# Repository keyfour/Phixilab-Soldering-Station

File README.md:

# Phixilab-Soldering-Station

Hardware desing for soldering station

* [Documentation](doc/README.md)

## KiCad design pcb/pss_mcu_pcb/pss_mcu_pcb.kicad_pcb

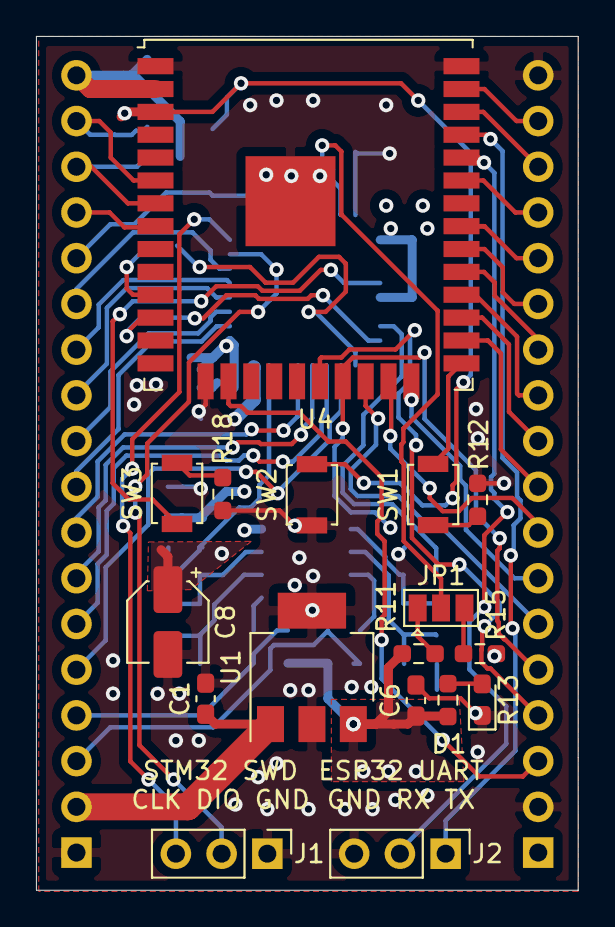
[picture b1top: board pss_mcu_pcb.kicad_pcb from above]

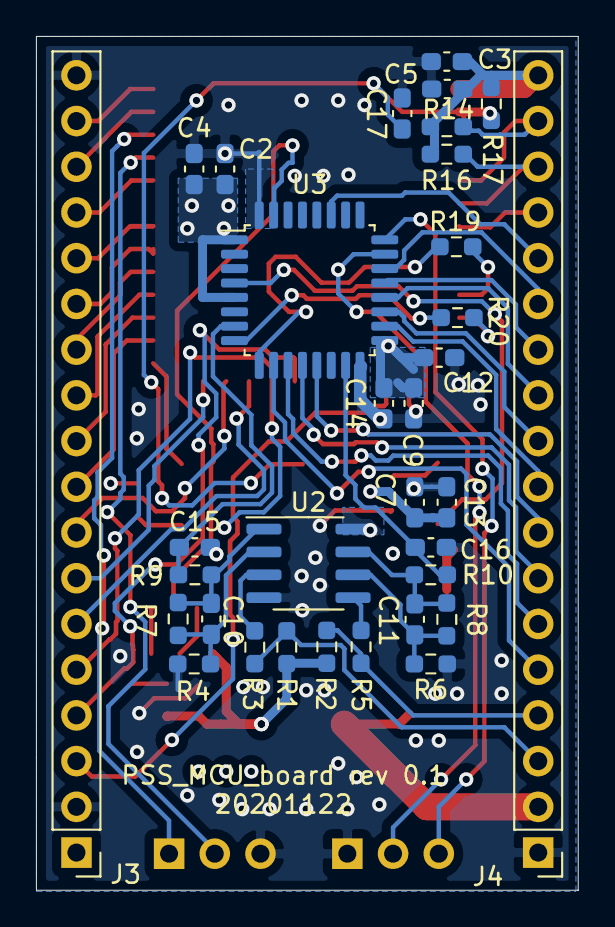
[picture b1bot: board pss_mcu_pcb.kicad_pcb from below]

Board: 4 copper layers, 30.1 x 47.4 mm, 50 parts (33 on the bottom side), 58 nets.

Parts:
C1: 0.47u; C_0603_1608Metric_Pad1.08x0.95mm_HandSolder
C2, C10, C11, C15, C16: 10n; C_0603_1608Metric_Pad1.08x0.95mm_HandSolder
C3, C17: 10u; C_0603_1608Metric_Pad1.08x0.95mm_HandSolder
C4: 1u; C_0603_1608Metric_Pad1.08x0.95mm_HandSolder
C5: 0.1u; C_0603_1608Metric_Pad1.08x0.95mm_HandSolder
C6: 33u; C_0603_1608Metric_Pad1.08x0.95mm_HandSolder
C7, C13: 0.15u; C_0603_1608Metric_Pad1.08x0.95mm_HandSolder
C8: 10u 16V; CP_Elec_4x5.3
C9, C12: 100n; C_0603_1608Metric_Pad1.08x0.95mm_HandSolder
C14: 4.7u; C_0603_1608Metric_Pad1.08x0.95mm_HandSolder
D1: LED; LED_0603_1608Metric_Pad1.05x0.95mm_HandSolder
J1: STM32_Prog; PinHeader_1x03_P2.54mm_Vertical
J2: UART_Prog; PinHeader_1x03_P2.54mm_Vertical
J3, J4: Conn_01x18; PinHeader_1x18_P2.54mm_Vertical
JP1: Jumper_NC_Dual; SolderJumper-3_P1.3mm_Open_Pad1.0x1.5mm
R1, R2, R7, R8: 100k; R_0603_1608Metric_Pad0.98x0.95mm_HandSolder
R3, R4, R5, R6, R9, R10, R11, R12, R15, R18: 1k; R_0603_1608Metric_Pad0.98x0.95mm_HandSolder
R13: 100; R_0603_1608Metric_Pad0.98x0.95mm_HandSolder
R14, R16: 10k; R_0603_1608Metric_Pad0.98x0.95mm_HandSolder
R17: 51k; R_0603_1608Metric_Pad0.98x0.95mm_HandSolder
R19, R20: 10; R_0603_1608Metric_Pad0.98x0.95mm_HandSolder
SW1: Boot; SW_SPST_B3U-1000P
SW2: EN; SW_SPST_B3U-1000P
SW3: SW_Push; SW_SPST_B3U-1000P
U1: LM3940IMP-3.3_NOPB; SOT-223
U2: LM358; SOIC-8_3.9x4.9mm_P1.27mm
U3: STM32F030K6Tx; LQFP-32_7x7mm_P0.8mm
U4: ESP32-WROOM-32U

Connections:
+3V3: C2.1, C3.1, C4.1, C5.1, C6.1, C7.1, C8.1, C9.1, C12.1, C13.1, C14.1, J3.1, J4.18, R1.1, R2.1, R11.2, R13.2, R14.1, R16.1, R17.1, U1.3, U2.8, U3.1, U3.5, U3.17, U4.2
+5V: C1.1, J4.2, U1.1
Boot: SW1.2, U4.25
DISP_CS: J3.17, U4.37
DISP_DC_RS: J3.15, U4.33
DISP_RST: J3.16, U4.36
DISP_SCK: J3.13, U4.30
DISP_SDI: J3.14, U4.31
DISP_SDO: J3.12, U4.29
DISP_T_CLK: J3.11, U4.28
DISP_T_CS: J3.10, U4.27
DISP_T_DIN: J3.9, U4.26
DISP_T_DO: J3.8, U4.23
DISP_T_IRQ: J3.7, U4.24
EN: C17.1, R17.2, SW2.2, U4.3
ESP32_UART_RX: R20.1, U4.12
ESP32_UART_TX: R19.1, U4.11
Fan_PWM: J4.12, U3.21
GND: C1.2, C2.2, C3.2, C4.2, C5.2, C6.2, C7.2, C8.2, C9.2, C12.2, C13.2, C14.2, C15.2, C16.2, C17.2, D1.1, J1.1, J2.3, J3.2, J3.18, J4.1, R4.1, R6.1, R12.2, R15.1, R18.1, SW2.1, U1.2, U1.4, U2.4, U3.16, U3.32, U4.1, U4.15, U4.38, U4.39
Heater_PWM: J4.7, U3.12
HotA_Enc_A: J4.8, U3.13
HotA_Enc_B: J4.14, U3.27
HotA_Switch: J4.11, U3.20
Hot_Air_Reed: J4.13, U3.22
Hot_Air_Themp_ADC: C16.1, R10.1, U3.15
Hot_Air_Therm_Pos: J4.4, R2.2, R5.2
Iron_Themp_ADC: C15.1, R9.1, U3.7
Iron_Therm_Pos: J4.3, R1.2, R3.2
Main_Enc_A: J4.17, R14.2, U4.6
Main_Enc_B: J4.16, R16.2, U4.7
Main_Switch: J4.15, U4.8
unnamed: C10.1, R4.2, R7.2, U2.2
unnamed: C10.2, R7.1, R9.2, U2.1
unnamed: C11.1, R6.2, R8.2, U2.6
unnamed: C11.2, R8.1, R10.2, U2.7
unnamed: D1.2, R13.1
unnamed: JP1.1, R11.1
unnamed: JP1.3, R15.2
unnamed: R3.1, U2.3
unnamed: R5.1, U2.5
unnamed: R12.1, SW1.1
unnamed: R18.2, SW3.2
RXD: J2.2, U4.34
SD_CS: J3.3, U4.16
SD_SCK: J3.4, U4.20
SD_SDI: J3.5, U4.21
SD_SDO: J3.6, U4.22
STM_BOOT: JP1.2, U3.31
STM_RST: SW3.1, U3.4
STM_SWCLK: J1.3, U3.24
STM_SWDIO: J1.2, U3.23
STM_UART_RX: R19.2, U3.9
STM_UART_TX: R20.2, U3.8
Sold_Enc_A: J4.10, U3.19
Sold_Enc_B: J4.9, U3.18
Sold_PWM: J4.5, U3.10
Sold_Switch: J4.6, U3.11
TXD: J2.1, U4.35

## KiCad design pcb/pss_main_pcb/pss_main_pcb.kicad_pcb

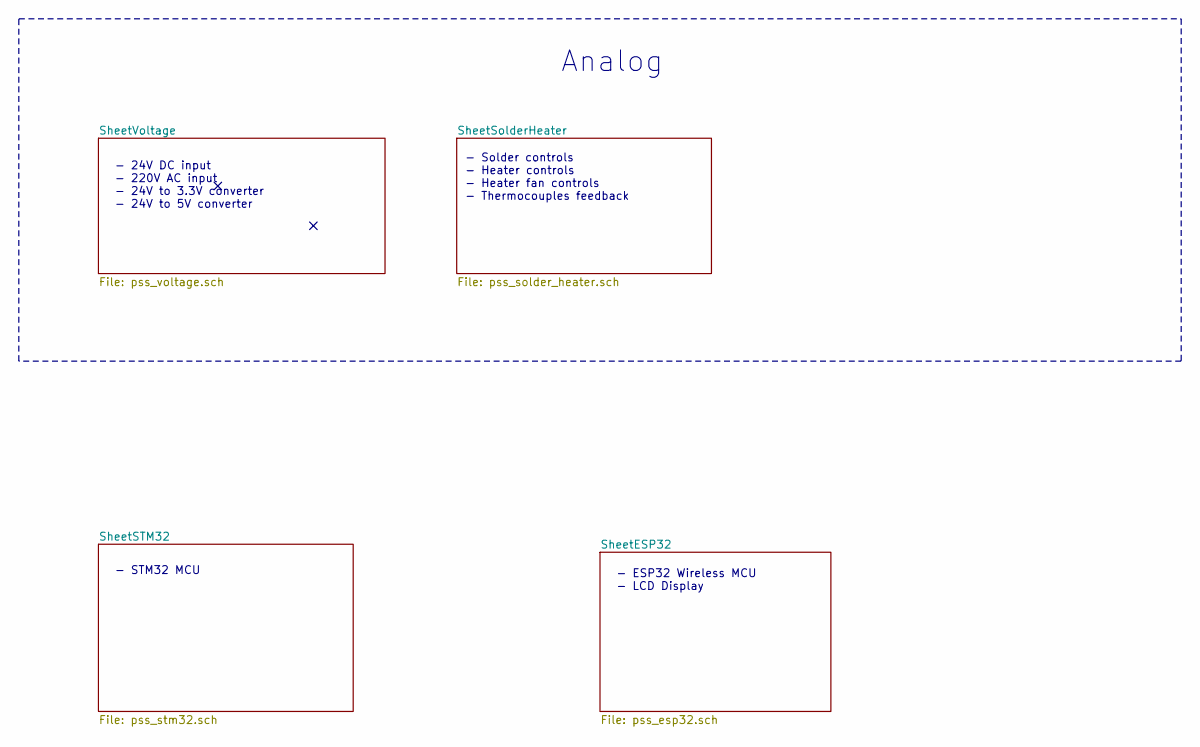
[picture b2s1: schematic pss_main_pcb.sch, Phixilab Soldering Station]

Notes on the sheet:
- 24V DC input - 220V AC input - 24V to 3.3V converter - 24V to 5V converter
- Solder controls - Heater controls - Heater fan controls - Thermocouples feedback
Analog
- STM32 MCU
- ESP32 Wireless MCU - LCD Display

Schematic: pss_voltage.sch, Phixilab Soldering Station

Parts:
C1: 470u 35V; CP_Elec_10x10.5
C2: 270u 10V; CP_Elec_8x10.5
C3: 330u 10V; CP_Elec_8x10.5
D1, D2: SS34; D_SMA_Handsoldering
J1: 24V DC Input; AMASS_XT30U-F_1x02_P5.0mm_Vertical
J2: 220V AC Input; SolderWire-2.5sqmm_1x03_P7.2mm_D2.4mm_OD3.6mm
L1: 68u; L_Taiyo-Yuden_NR-30xx_HandSoldering
L2: 47u; L_Taiyo-Yuden_NR-30xx_HandSoldering
R1: 1k; R_1206_3216Metric_Pad1.42x1.75mm_HandSolder
U1: LM2596S-5; TO-263-5_TabPin3
U2: LM2596S-3.3; TO-263-5_TabPin3

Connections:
220V_Heater2: J2.2; also elsewhere on the board
220_AC1: J2.3; also elsewhere on the board
+3V3: U2.3; also elsewhere on the board
BOOST: U1.6; also elsewhere on the board
FB: U1.12; also elsewhere on the board
GNDPWR: J2.1; also elsewhere on the board
SHDN: D1.3, R1.2, U1.15; also elsewhere on the board

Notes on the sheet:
Voltage Inputs
5V Regulator Output
3.3V Regulator Output

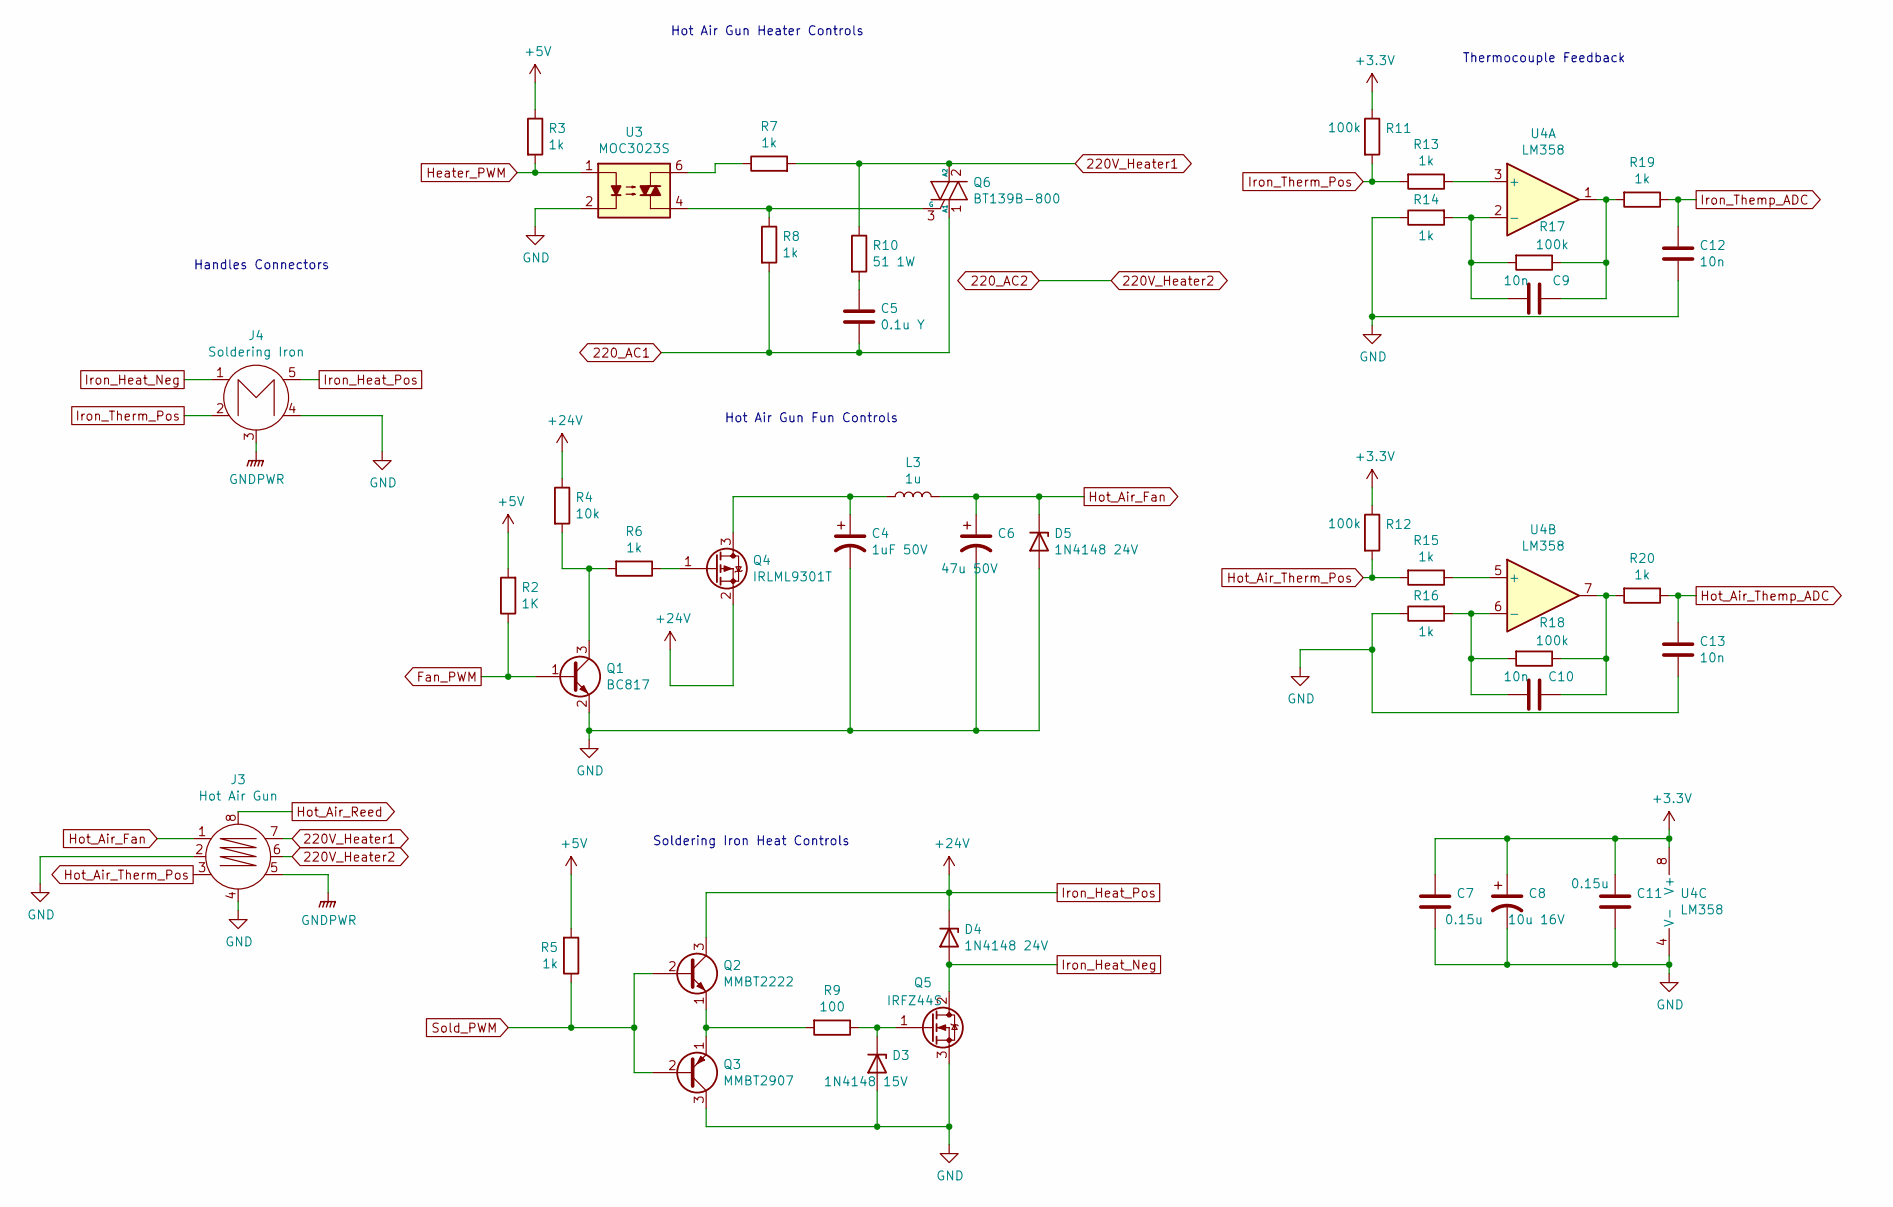
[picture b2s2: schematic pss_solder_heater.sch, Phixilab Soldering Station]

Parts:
C4: 1uF 50V; CP_Elec_4x5.4
C5: 0.1u Y; C_Rect_L10.0mm_W2.5mm_P7.50mm_MKS4
C6: 47u 50V; CP_Elec_8x10.5
C7, C11: 0.15u; C_1206_3216Metric_Pad1.42x1.75mm_HandSolder
C8: 10u 16V; CP_Elec_4x5.4
C9, C10, C12, C13: 10n; C_1206_3216Metric_Pad1.42x1.75mm_HandSolder
D3: 1N4148 15V; D_1206_3216Metric_Pad1.42x1.75mm_HandSolder
D4, D5: 1N4148 24V; D_1206_3216Metric_Pad1.42x1.75mm_HandSolder
J3: Hot Air Gun; GX16-8
J4: Soldering Iron; GX16-5
L3: 1u; L_Taiyo-Yuden_NR-30xx_HandSoldering
Q1: BC817; SOT-23_Handsoldering
Q2: MMBT2222; SOT-23_Handsoldering
Q3: MMBT2907; SOT-23_Handsoldering
Q4: IRLML9301T; SOT-23_Handsoldering
Q5: IRFZ44S; TO-263-2
Q6: BT139B-800; D2PAK-3
R2: 1K; R_1206_3216Metric_Pad1.42x1.75mm_HandSolder
R3, R5, R6, R7, R8, R13, R14, R15, R16, R19, R20: 1k; R_1206_3216Metric_Pad1.42x1.75mm_HandSolder
R4: 10k; R_1206_3216Metric_Pad1.42x1.75mm_HandSolder
R9: 100; R_1206_3216Metric_Pad1.42x1.75mm_HandSolder
R10: 51 1W; R_2512_6332Metric_Pad1.52x3.35mm_HandSolder
R11, R12, R17, R18: 100k; R_1206_3216Metric_Pad1.42x1.75mm_HandSolder
U3: MOC3023S; SOT254P1016X460-6N
U4: LM358; SOIC-8_3.9x4.9mm_P1.27mm

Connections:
220V_Heater1: J3.7, Q6.2 (A2), R7.2, R10.1
220V_Heater2: J3.6; also elsewhere on the board
220_AC1: C5.2, Q6.1 (A1), R8.2; also elsewhere on the board
+3V3: C7.1, C8.1, C11.1, R11.1, R12.1, U4.8 (V+); also elsewhere on the board
Fan_PWM: Q1.1 (B), R2.1; also elsewhere on the board
GNDPWR: J3.5, J4.3; also elsewhere on the board
Heater_PWM: R3.2, U3.1; also elsewhere on the board
Hot_Air_Fan: C6.1, D5.1 (K), J3.1, L3.2
Hot_Air_Reed: J3.8; also elsewhere on the board
Hot_Air_Themp_ADC: C13.1, R20.1; also elsewhere on the board
Hot_Air_Therm_Pos: J3.3, R12.2, R15.2
Iron_Heat_Neg: D4.2 (A), J4.1, Q5.2 (D)
Iron_Themp_ADC: C12.1, R19.1; also elsewhere on the board
Iron_Therm_Pos: J4.2, R11.2, R13.2
unnamed: C4.1, L3.1, Q4.3 (D)
unnamed: C5.1, R10.2
unnamed: C9.1, R14.2, R17.2, U4.2 (-)
unnamed: C9.2, R17.1, R19.2, U4.1
unnamed: C10.1, R16.2, R18.2, U4.6 (-)
unnamed: C10.2, R18.1, R20.2, U4.7
unnamed: D3.1 (K), Q5.1 (G), R9.1
unnamed: Q1.3 (C), R4.2, R6.2
unnamed: Q2.1 (E), Q3.1 (E), R9.2
unnamed: Q4.1 (G), R6.1
unnamed: Q6.3 (G), R8.1, U3.4
unnamed: R7.1, U3.6
unnamed: R13.1, U4.3 (+)
unnamed: R15.1, U4.5 (+)
Sold_PWM: Q2.2 (B), Q3.2 (B), R5.1; also elsewhere on the board

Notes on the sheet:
Hot Air Gun Heater Controls
Hot Air Gun Fun Controls
Soldering Iron Heat Controls
Thermocouple Feedback
Handles Connectors

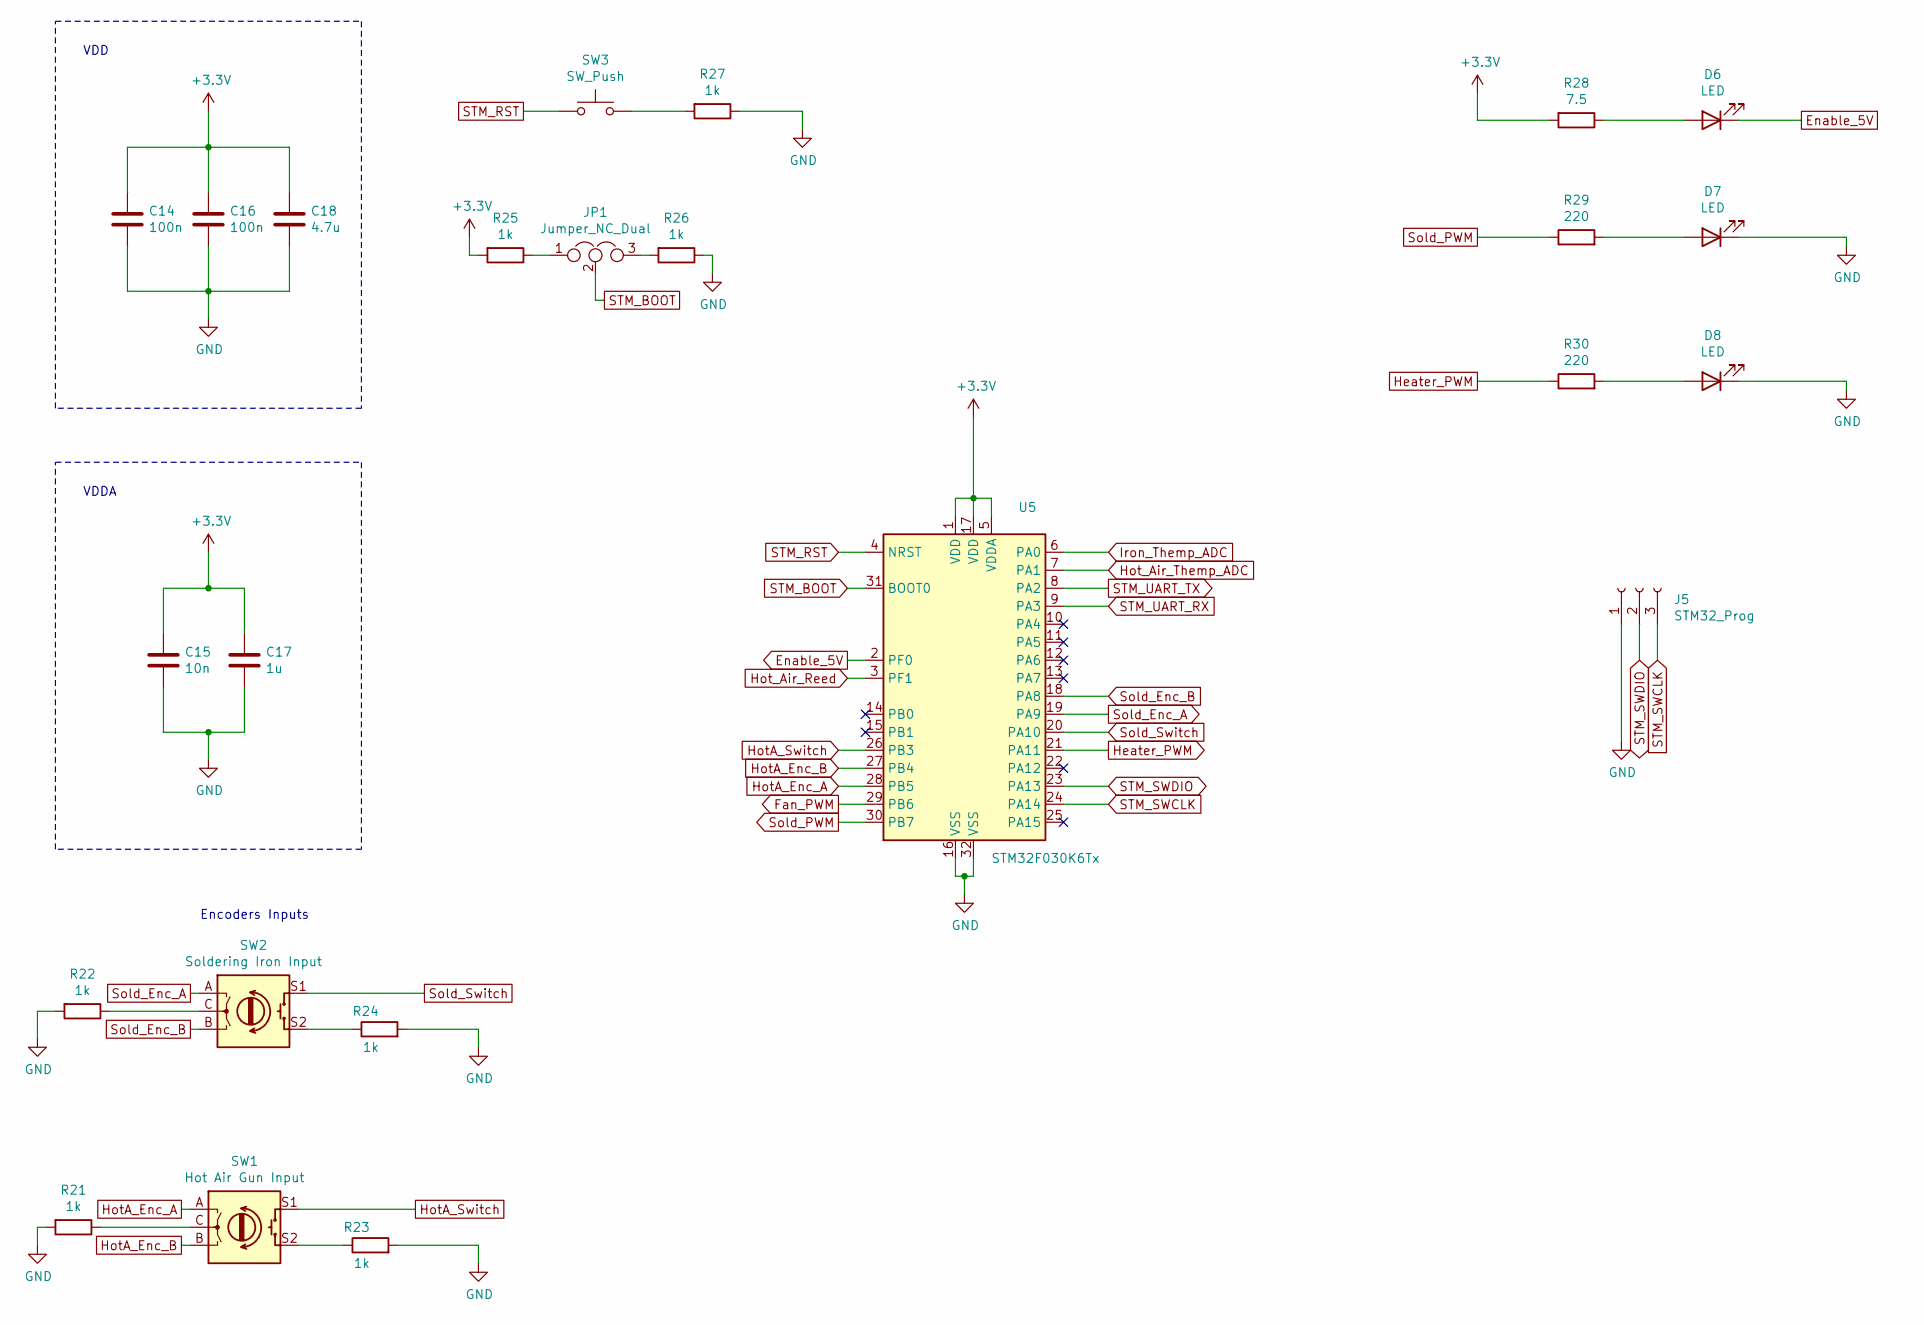
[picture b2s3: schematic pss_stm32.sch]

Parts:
C14, C16: 100n; C_1206_3216Metric_Pad1.42x1.75mm_HandSolder
C15: 10n; C_1206_3216Metric_Pad1.42x1.75mm_HandSolder
C17: 1u; C_1206_3216Metric_Pad1.42x1.75mm_HandSolder
C18: 4.7u; C_1206_3216Metric_Pad1.42x1.75mm_HandSolder
D6, D7, D8: LED; LED_D5.0mm
J5: STM32_Prog; PinHeader_1x03_P2.54mm_Vertical
JP1: Jumper_NC_Dual; SolderJumper-3_P1.3mm_Open_Pad1.0x1.5mm
R21, R22, R23, R24, R25, R26, R27: 1k; R_1206_3216Metric_Pad1.42x1.75mm_HandSolder
R28: 7.5; R_1206_3216Metric_Pad1.42x1.75mm_HandSolder
R29, R30: 220; R_1206_3216Metric_Pad1.42x1.75mm_HandSolder
SW1: Hot Air Gun Input; RotaryEncoder_Alps_EC11E-Switch_Vertical_H20mm
SW2: Soldering Iron Input; RotaryEncoder_Alps_EC11E-Switch_Vertical_H20mm
SW3: SW_Push; SW_SPST_B3S-1000
U5: STM32F030K6Tx; LQFP-32_7x7mm_P0.8mm

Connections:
+3V3: C14.1, C15.1, C16.1, C17.1, C18.1, R25.2, R28.2, U5.1 (VDD), U5.5 (VDDA), U5.17 (VDD); also elsewhere on the board
Enable_5V: D6.1 (K), U5.2 (PF0), U5.25 (PA15)
Fan_PWM: U5.29 (PB6); also elsewhere on the board
Heater_PWM: R30.1, U5.21 (PA11); also elsewhere on the board
HotA_Enc_A: SW1.A, U5.28 (PB5)
HotA_Enc_B: SW1.B, U5.27 (PB4)
HotA_Switch: SW1.S1, U5.26 (PB3)
Hot_Air_Reed: U5.3 (PF1); also elsewhere on the board
Hot_Air_Themp_ADC: U5.7 (PA1); also elsewhere on the board
Iron_Themp_ADC: U5.6 (PA0); also elsewhere on the board
unnamed: D6.2 (A), R28.1
unnamed: D7.2 (A), R29.2
unnamed: D8.2 (A), R30.2
unnamed: JP1.1, R25.1
unnamed: JP1.3, R26.2
unnamed: R21.1, SW1.C
unnamed: R22.1, SW2.C
unnamed: R23.1, SW1.S2
unnamed: R24.1, SW2.S2
unnamed: R27.2, SW3.2
STM_BOOT: JP1.2, U5.31 (BOOT0)
STM_RST: SW3.1, U5.4 (NRST)
STM_SWCLK: J5.3, U5.24 (PA14)
STM_SWDIO: J5.2, U5.23 (PA13)
STM_UART_RX: U5.9 (PA3); also elsewhere on the board
STM_UART_TX: U5.8 (PA2); also elsewhere on the board
Sold_Enc_A: SW2.A, U5.19 (PA9)
Sold_Enc_B: SW2.B, U5.18 (PA8)
Sold_PWM: R29.1, U5.30 (PB7); also elsewhere on the board
Sold_Switch: SW2.S1, U5.20 (PA10)

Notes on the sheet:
VDD
VDDA
Encoders Inputs

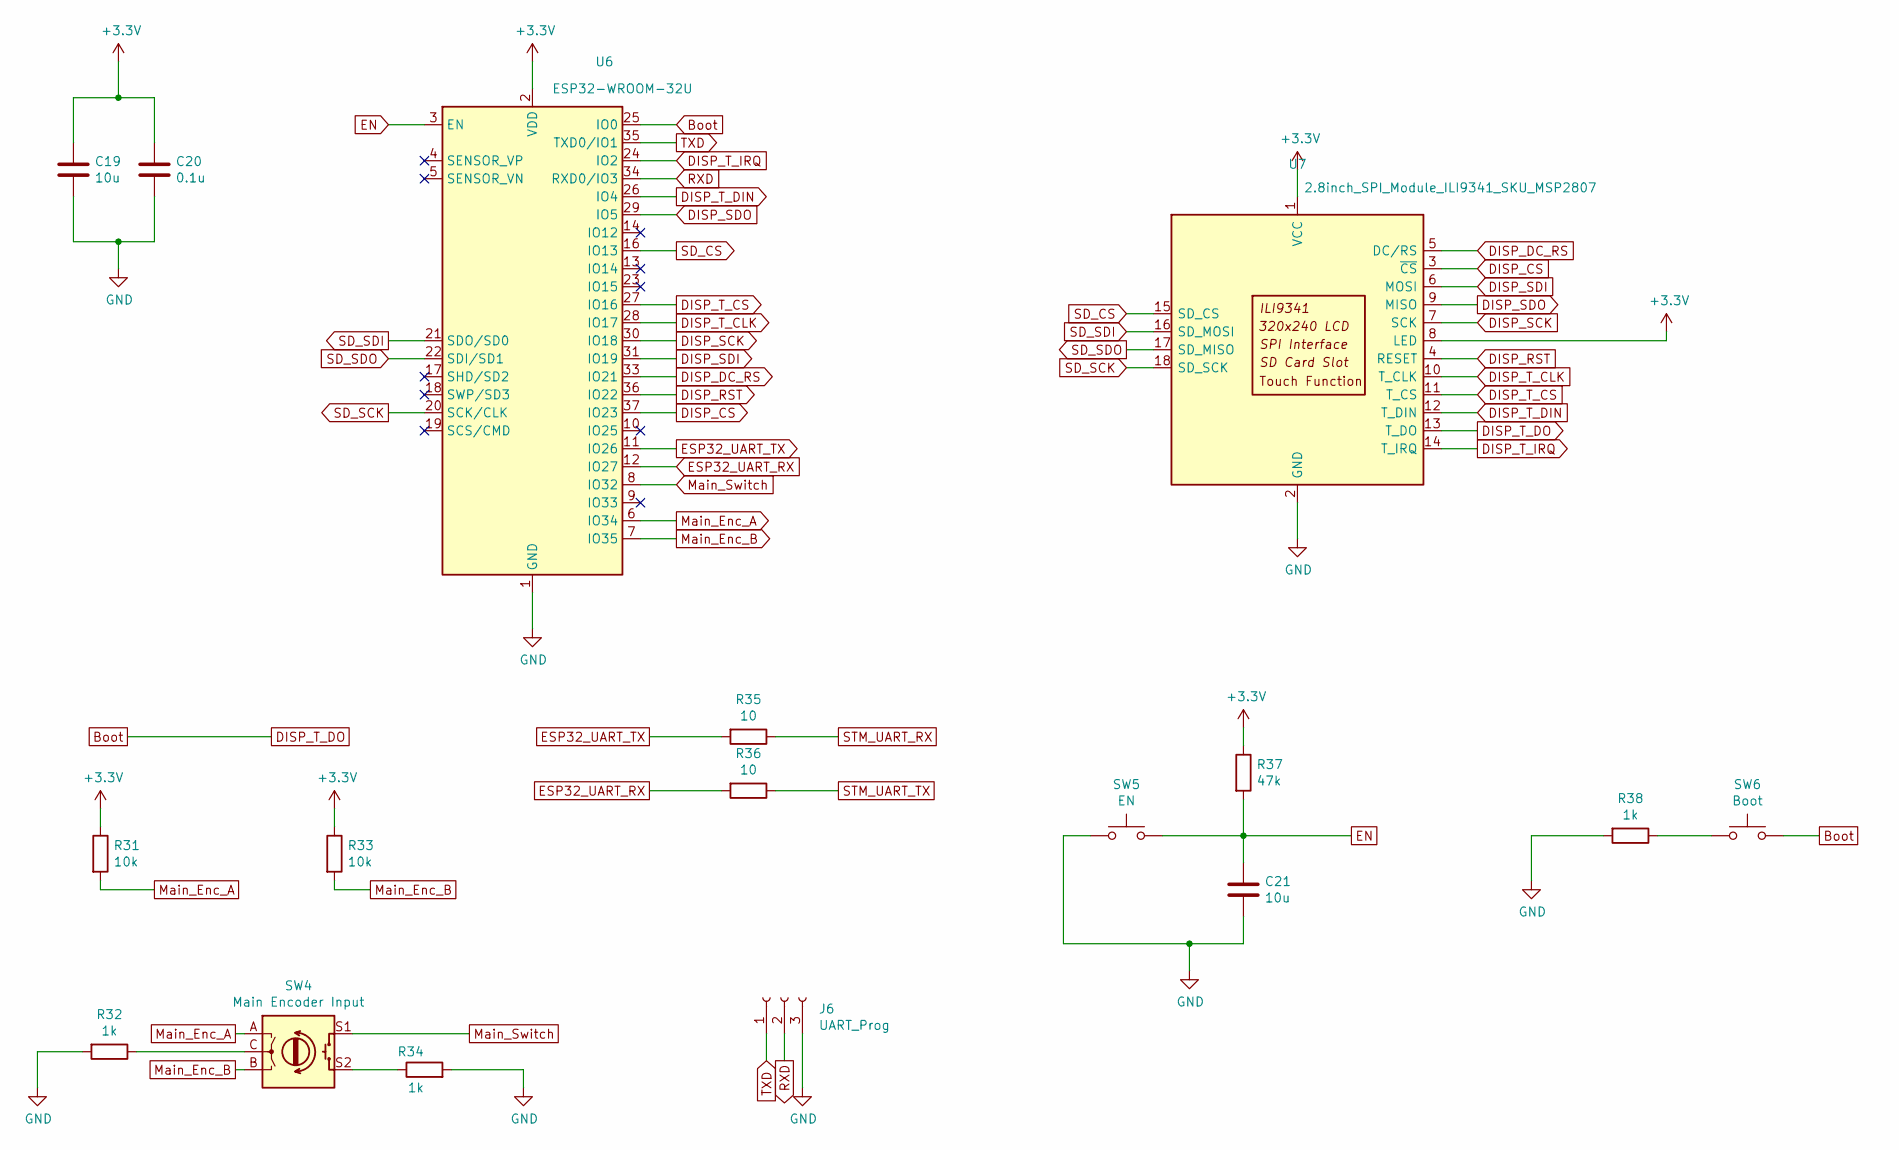
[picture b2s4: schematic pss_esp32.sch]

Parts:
C19, C21: 10u; C_1206_3216Metric_Pad1.42x1.75mm_HandSolder
C20: 0.1u; C_1206_3216Metric_Pad1.42x1.75mm_HandSolder
J6: UART_Prog; PinHeader_1x03_P2.54mm_Vertical
R31, R33: 10k; R_1206_3216Metric_Pad1.42x1.75mm_HandSolder
R32, R34, R38: 1k; R_1206_3216Metric_Pad1.42x1.75mm_HandSolder
R35, R36: 10; R_1206_3216Metric_Pad1.42x1.75mm_HandSolder
R37: 47k; R_1206_3216Metric_Pad1.42x1.75mm_HandSolder
SW4: Main Encoder Input; RotaryEncoder_Alps_EC11E-Switch_Vertical_H20mm
SW5: EN; SW_SPST_B3S-1000
SW6: Boot; SW_SPST_B3S-1000
U6: ESP32-WROOM-32U
U7: 2.8inch_SPI_Module_ILI9341_SKU_MSP2807; MSP2807

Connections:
+3V3: C19.1, C20.1, R31.1, R33.1, R37.1, U6.2 (VDD), U7.1 (VCC), U7.8 (LED); also elsewhere on the board
Boot: SW6.2, U6.25 (IO0), U7.13 (T_DO)
DISP_CS: U6.37 (IO23), U7.3 (~CS)
DISP_DC_RS: U6.33 (IO21), U7.5 (DC/RS)
DISP_RST: U6.36 (IO22), U7.4 (RESET)
DISP_SCK: U6.30 (IO18), U7.7 (SCK)
DISP_SDI: U6.31 (IO19), U7.6 (MOSI)
DISP_SDO: U6.29 (IO5), U7.9 (MISO)
DISP_T_CLK: U6.28 (IO17), U7.10 (T_CLK)
DISP_T_CS: U6.27 (IO16), U7.11 (T_CS)
DISP_T_DIN: U6.26 (IO4), U7.12 (T_DIN)
DISP_T_IRQ: U6.24 (IO2), U7.14 (T_IRQ)
EN: C21.1, R37.2, SW5.2, U6.3 (EN)
ESP32_UART_RX: R36.2, U6.12 (IO27)
ESP32_UART_TX: R35.2, U6.11 (IO26)
Main_Enc_A: R31.2, SW4.A, U6.6 (IO34)
Main_Enc_B: R33.2, SW4.B, U6.7 (IO35)
Main_Switch: SW4.S1, U6.8 (IO32)
unnamed: R32.1, SW4.C
unnamed: R34.1, SW4.S2
unnamed: R38.1, SW6.1
RXD: J6.2, U6.34 (RXD0/IO3)
SD_CS: U6.16 (IO13), U7.15 (SD_CS)
SD_SCK: U6.20 (SCK/CLK), U7.18 (SD_SCK)
SD_SDI: U6.21 (SDO/SD0), U7.16 (SD_MOSI)
SD_SDO: U6.22 (SDI/SD1), U7.17 (SD_MISO)
STM_UART_RX: R35.1; also elsewhere on the board
STM_UART_TX: R36.1; also elsewhere on the board
TXD: J6.1, U6.35 (TXD0/IO1)

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
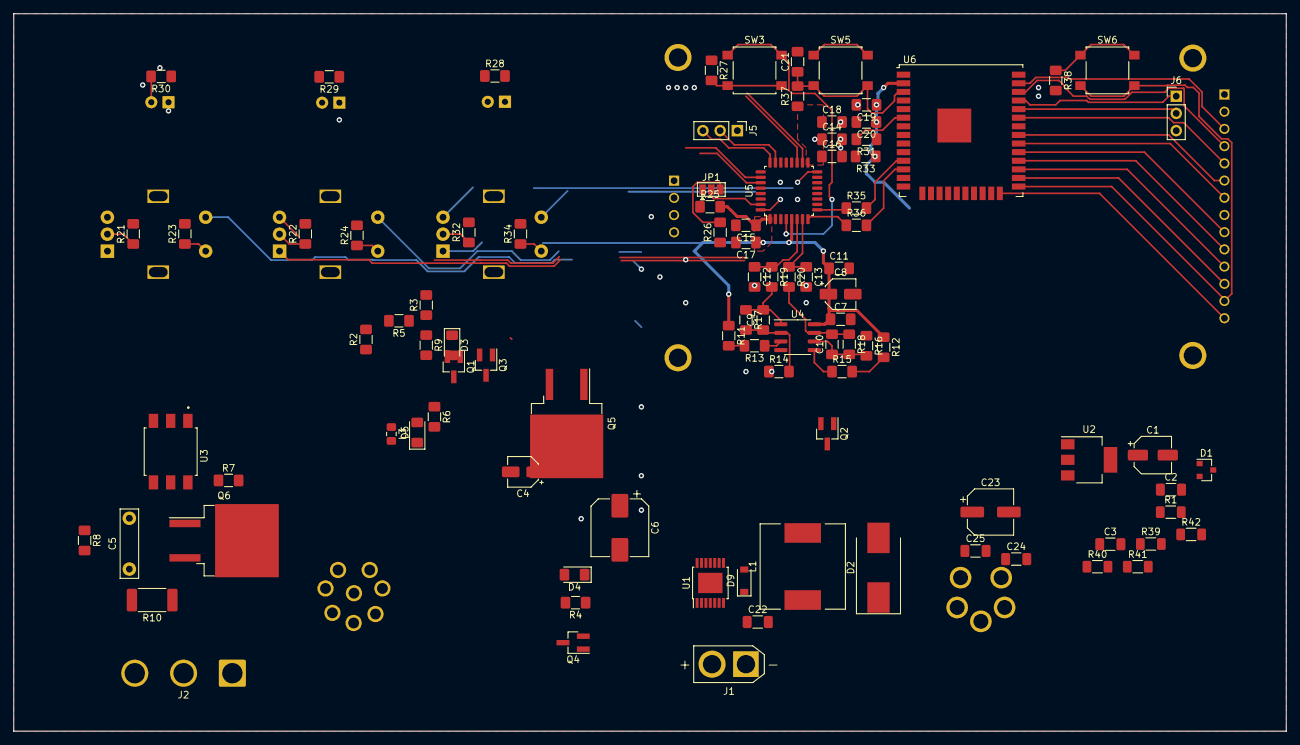
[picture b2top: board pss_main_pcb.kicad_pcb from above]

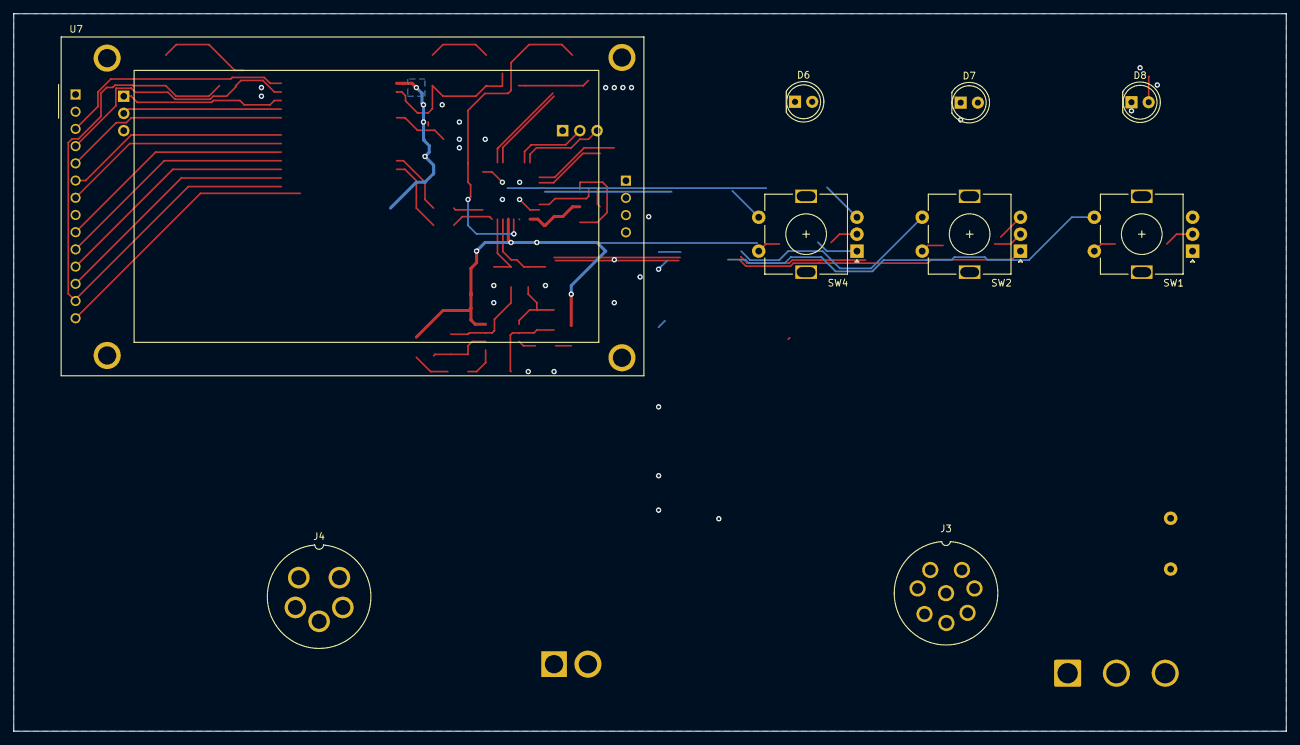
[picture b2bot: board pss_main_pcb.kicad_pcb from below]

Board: 2 copper layers, 187.8 x 105.9 mm, 104 parts (9 on the bottom side), 87 nets.

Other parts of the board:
C22: 0.68u; C_1206_3216Metric_Pad1.33x1.80mm_HandSolder
C23: 100u 10v; CP_Elec_6.3x7.7
C24: 0.47u; C_1206_3216Metric_Pad1.33x1.80mm_HandSolder
C25: 33u; C_1206_3216Metric_Pad1.33x1.80mm_HandSolder
D9: MMSD914T1; D_SOD-123
R39: 10k; R_1206_3216Metric_Pad1.30x1.75mm_HandSolder
R40: 3.3k; R_1206_3216Metric_Pad1.30x1.75mm_HandSolder
R41: 15.4k; R_1206_3216Metric_Pad1.30x1.75mm_HandSolder
R42: 4.99k; R_1206_3216Metric_Pad1.30x1.75mm_HandSolder

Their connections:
+3V3: C25.1; also elsewhere on the board
BOOST: C22.1, D9.1; also elsewhere on the board
FB: R41.2, R42.1; also elsewhere on the board
SHDN: R39.1; also elsewhere on the board

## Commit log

2020-03-14 Add preliminary structure
2020-03-14 Fix path
2020-03-15 Changes device structure
    * change power sources
    * add button
    * rename main _MCU_
2020-03-15 Fix structure
    Change interface board low voltage domain name.
2020-03-15 Add description
2020-03-15 Fix typo
2020-03-15 Change readme files
2020-03-15 Fix typo in path
2020-04-03 Change device structure
2020-04-03 Change device structure description
2020-04-04 Add components preliminary BOM
2020-04-04 Fix structure and add preliminary BOM
2020-04-04 Add components to preliminary BOM
2020-04-04 Add KiCad project and voltage inputs in schematics
2020-04-04 Add connectors symbols
2020-04-04 Change connectors pins numbers
2020-04-04 Add connectors to schematics
2020-04-04 Add rotary encoders to schematics
2020-04-04 Add custom components
2020-04-11 Add 5v domain
2020-04-11 Change description
2020-04-11 Change dc-dc converters in structure
2020-04-11 Add voltage converters and soldering heater
2020-04-12 Fix schematics
2020-04-12 Add 220v controls schematics
2020-04-12 Add small changes to schematics
2020-04-19 Add fan controls schematics
2020-04-19 Add thermocouple feedback schematics
2020-04-19 Add project file
2020-04-19 Add hierarchy lists
2020-04-19 Change lists configurations
2020-04-19 Add new list
2020-05-03 Add stm32 schematics
2020-05-03 Add ESP32 list
2020-05-17 Add display library
2020-05-17 Add ESP32 to display and STM32 connections
2020-05-23 Add footprints for connectors
2020-05-23 Add footprints for AC controls components
2020-05-23 Change safety capacitor footprint
2020-05-24 Add footprints for power sources components
2020-05-24 Add footprints for heaters controls
2020-05-24 Add some more footprints
2020-05-31 Add footprints
2020-05-31 Create netlist and place some components
2020-06-07 Change footprints
2020-06-14 Change footprints and place some new components
2020-06-20 Finish preliminary placement for components
2020-06-21 Started pcb routing
2020-06-21 Intermediate changes
2020-06-21 Change routing
2020-07-19 Add new routes
2020-07-24 Add routes for low power rails
2020-07-31 Change routes
2020-08-16 Add encoders routes
2020-08-16 Add routes and fill planes
2020-09-13 Change components placement and routes
2020-09-19 Add display 3D model for PCB design
2020-09-19 Add image to readme
2020-09-19 Add connector 3D model
2020-10-10 Add 3D models and totaly redesign PCB
2020-10-25 Add processor board
2020-11-01 Change schematics
2020-11-01 Add PCB
2020-11-07 Change elements placement
2020-11-22 Fix design issues
2020-11-22 Add name
2020-12-03 Add files for manufacturing
2020-12-13 Fix gerber files
2021-01-07 Add assembly drawings
    Remove unnecessary files
2021-01-07 Change resistor value
